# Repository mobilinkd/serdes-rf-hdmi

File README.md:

# serdes-rf-hdmi

HDMI test fixture for TMDS to single-ended SMA for RF testing.

This board is designed to test RF input and output using TMDS signals from the
Pynq-Z2 board's HDMI port.  It capacitively couples the clock signal for use
as an NCO (this is used in a single-ended output/input mode).  And it provides
two identical differentially-coupled signals for either RF input or RF output.

The RF signals are filtered by a 4th order Chebyshev bandpass filter.  The
RF is coupled to the TMDS pair via a center-tapped 1:1 RF transformer.  The
center tap is connected to ground via a 50 Ohm resistor.

The filter is designed for the 2m amateur radio band, but can easily be
adapted to other bands of interest.  It is important to have at a minimum
a low-pass filter with the 2λ at down least -40dB to prevent aliasing.

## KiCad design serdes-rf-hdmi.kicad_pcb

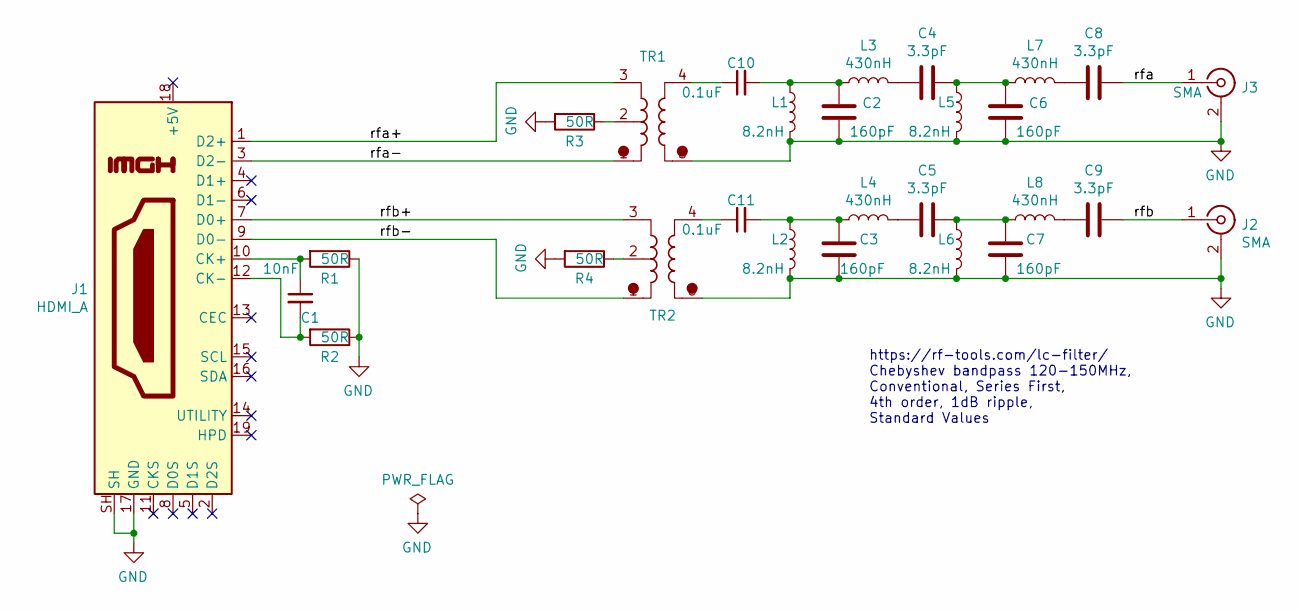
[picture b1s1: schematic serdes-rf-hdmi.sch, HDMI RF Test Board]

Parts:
C1: 10nF; C_0603_1608Metric
C2, C3, C6, C7: 160pF; C_0603_1608Metric_Pad1.08x0.95mm_HandSolder
C4, C5, C8, C9: 3.3pF; C_0603_1608Metric_Pad1.08x0.95mm_HandSolder
C10, C11: 0.1uF; C_0603_1608Metric
J1: HDMI_A; HDMI_A_Contact_Technology_HDMI-19APL2_Horizontal
J2, J3: SMA; SMA_Samtec_SMA-J-P-X-ST-EM1_EdgeMount
L1, L2, L5, L6: 8.2nH; L_0603_1608Metric_Pad1.05x0.95mm_HandSolder
L3, L4, L7, L8: 430nH; L_0603_1608Metric_Pad1.05x0.95mm_HandSolder
R1, R2, R3, R4: 50R; R_0805_2012Metric
TR1, TR2: TC1-1TX+; XFMR_TC1-1-13M+

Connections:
/rfa: C8.1, J3.1 (In)
/rfa+: J1.1 (D2+), TR1.3
/rfa-: J1.3 (D2-), TR1.1
/rfb: C9.1, J2.1 (In)
/rfb+: J1.7 (D0+), TR2.3
/rfb-: J1.9 (D0-), TR2.1
GND: C2.2, C3.2, C6.2, C7.2, J1.17 (GND), J1.SH, J2.2 (Ext), J3.2 (Ext), L1.2, L2.2, L5.2, L6.2, R1.1, R2.1, R3.2, R4.2, TR1.6, TR2.6
unnamed: C1.1, J1.10 (CK+), R1.2
unnamed: C1.2, J1.12 (CK-), R2.2
unnamed: C4.1, C6.1, L5.1, L7.1
unnamed: C4.2, L3.2
unnamed: C5.1, C7.1, L6.1, L8.1
unnamed: C5.2, L4.2
unnamed: C8.2, L7.2
unnamed: C9.2, L8.2
unnamed: C10.1, TR1.4
unnamed: C2.1, C10.2, L1.1, L3.1
unnamed: C11.1, TR2.4
unnamed: C3.1, C11.2, L2.1, L4.1
unnamed: R3.1, TR1.2
unnamed: R4.1, TR2.2

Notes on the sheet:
https://rf-tools.com/lc-filter/ Chebyshev bandpass 120-150MHz, Conventional, Series First, 4th order, 1dB ripple, Standard Values

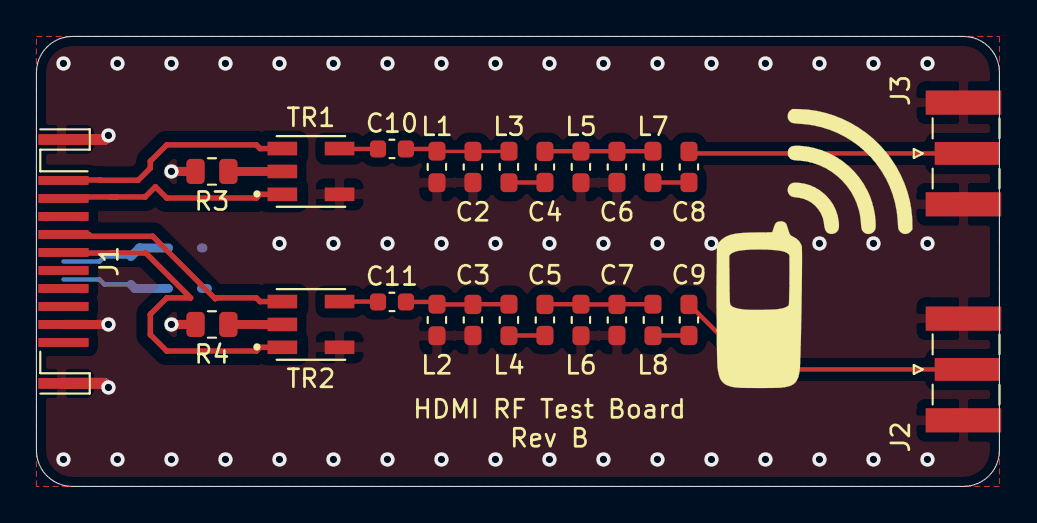
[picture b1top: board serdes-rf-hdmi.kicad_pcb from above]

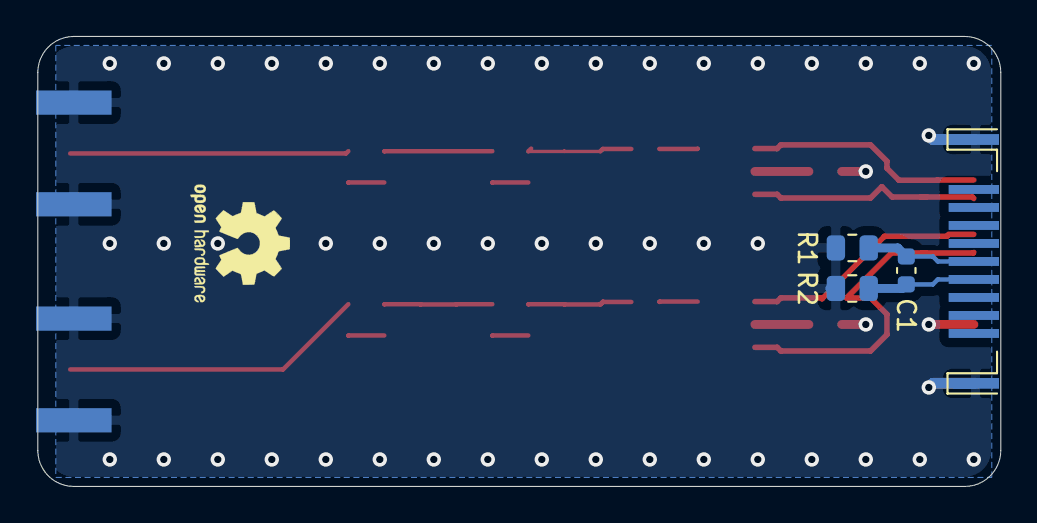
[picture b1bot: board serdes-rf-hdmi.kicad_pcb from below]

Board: 4 copper layers, 53.5 x 25.0 mm, 29 parts (3 on the bottom side), 21 nets.

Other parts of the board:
G1: LOGO; Mobilinkd_Logo

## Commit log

2021-08-29 Initial commit.
2021-08-30 Add Gerbers and update README.
2021-10-07 Start of rev B design.
2021-10-08 Rev B complete
2021-10-08 Update one track and generate Gerbers.
2021-10-10 Fix bandpass filter and add coupling caps. Update image and README.
2021-10-10 Trivial changes to layout.
